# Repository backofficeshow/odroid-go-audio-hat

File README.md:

# odroid-go-audio-hat
An I2S Audio Hat for stereo sound from the odroid-go

UPDATE: The live build stream! https://youtu.be/j9-wCR7noaQ

1) A Manual Mod Was Made:

https://youtu.be/pp_DPHiUhcc

2) A SPI option conceived and failed:

https://youtu.be/Ehr8WgxajMo

https://www.youtube.com/watch?v=8DnR3sBm568

3) This forum thread provided the answers:

https://forum.odroid.com/viewtopic.php?f=158&t=31853&p=231227#p231227

crashoverride knows all the magic gpio runes!

4) The results are this archive!

https://www.youtube.com/watch?v=rQte53dfJiA

https://www.youtube.com/backofficeshow

Come chat with me on discord https://discord.gg/6UB4Zj7

Useful Links

PCM5102 Datasheet:

http://www.ti.com/lit/ds/slas764b/slas764b.pdf

Odroid-go Overview:

https://www.hardkernel.com/main/products/prdt_info.php?g_code=G152875062626

Odroid-go IO Information:

https://wiki.odroid.com/odroid_go/odroid_go#odroid-go_header_p2_description

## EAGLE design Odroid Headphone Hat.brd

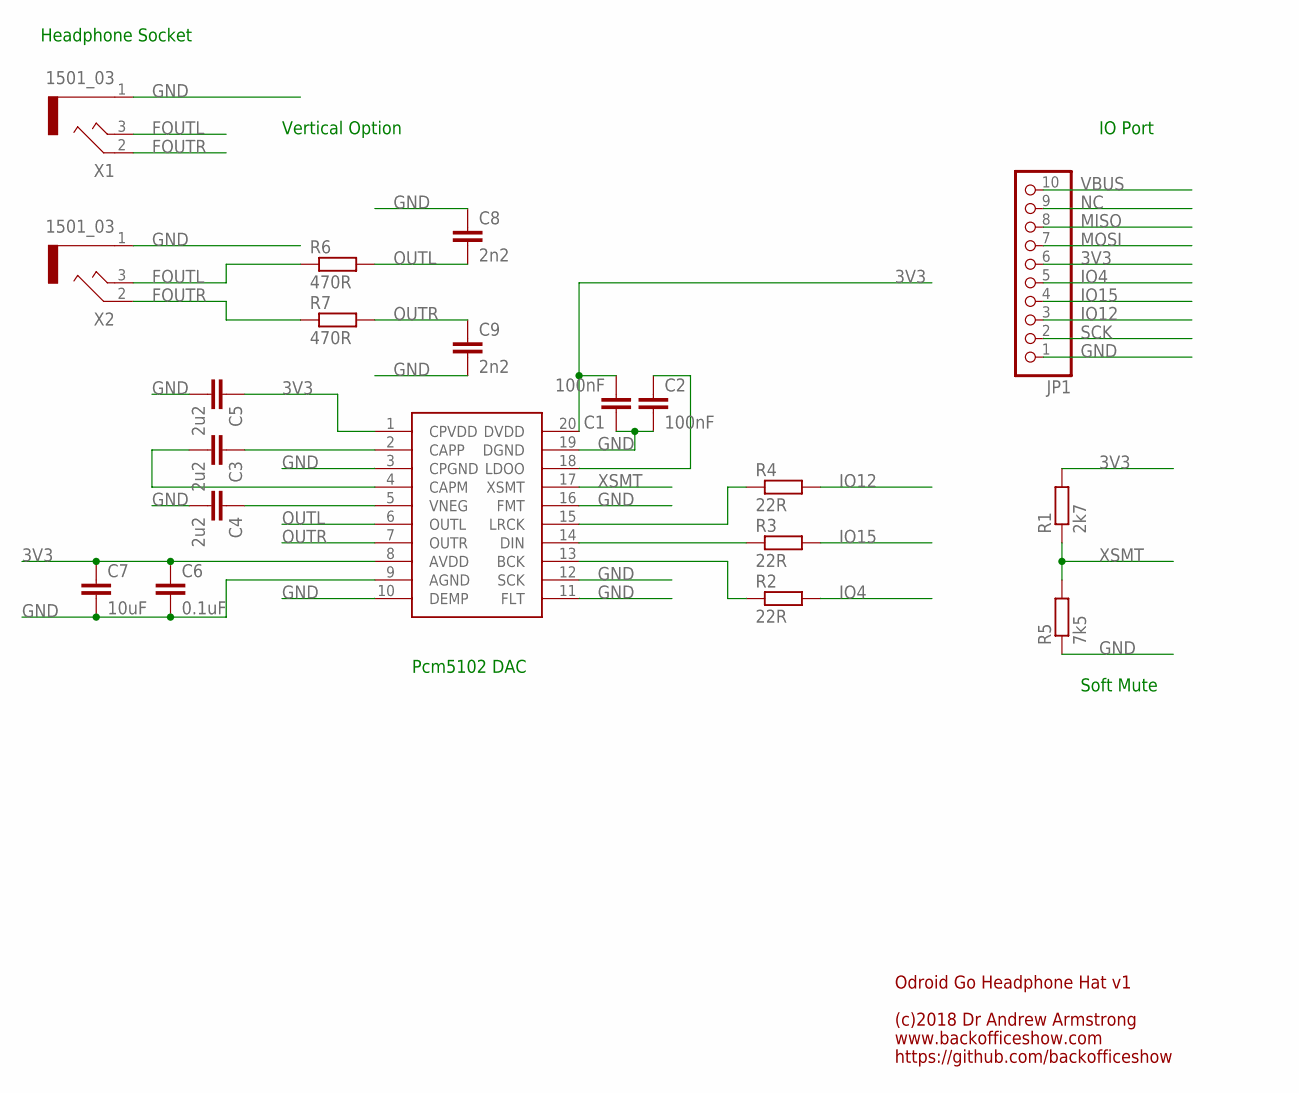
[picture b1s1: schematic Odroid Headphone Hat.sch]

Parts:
C1, C2: 100nF; C0603
C3, C4, C5: 2u2; C0603
C6: 0.1uF; C0603
C7: 10uF; C0603
C8, C9: 2n2; C0603
JP1: PINHD-1X10/90; 1X10/90
R1: 2k7; R0603
R2, R3, R4: 22R; R0603
R5: 7k5; R0603
R6, R7: 470R; R0603
U$1: PCM5102; TSSOP20
X1, X2: 1501_03

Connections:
3V3: C1.2, C5.1, C6.1, C7.1, JP1.6, R1.2, U$1.1 (CPVDD), U$1.8 (AVDD), U$1.20 (DVDD)
FOUTL: R6.1, X1.3, X2.3
FOUTR: R7.1, X1.2, X2.2
GND: C1.1, C2.2, C4.2, C5.2, C6.2, C7.2, C8.1, C9.2, JP1.1, R5.1, U$1.3 (CPGND), U$1.9 (AGND), U$1.10 (DEMP), U$1.11 (FLT), U$1.12 (SCK), U$1.16 (FMT), U$1.19 (DGND), X1.1, X2.1
IO4: JP1.5, R2.2
IO12: JP1.3, R4.2
IO15: JP1.4, R3.2
MISO: JP1.8
MOSI: JP1.7
unnamed: R2.1, U$1.13 (BCK)
unnamed: R3.1, U$1.14 (DIN)
unnamed: R4.1, U$1.15 (LRCK)
unnamed: C2.1, U$1.18 (LDOO)
unnamed: C3.1, U$1.2 (CAPP)
unnamed: C3.2, U$1.4 (CAPM)
unnamed: C4.1, U$1.5 (VNEG)
NC: JP1.9
OUTL: C8.2, R6.2, U$1.6 (OUTL)
OUTR: C9.1, R7.2, U$1.7 (OUTR)
SCK: JP1.2
VBUS: JP1.10
XSMT: R1.1, R5.2, U$1.17 (XSMT)

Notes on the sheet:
Odroid Go Headphone Hat v1
(c)2018 Dr Andrew Armstrong
www.backofficeshow.com
https://github.com/backofficeshow
Soft Mute
IO Port
Pcm5102 DAC
Headphone Socket
Vertical Option

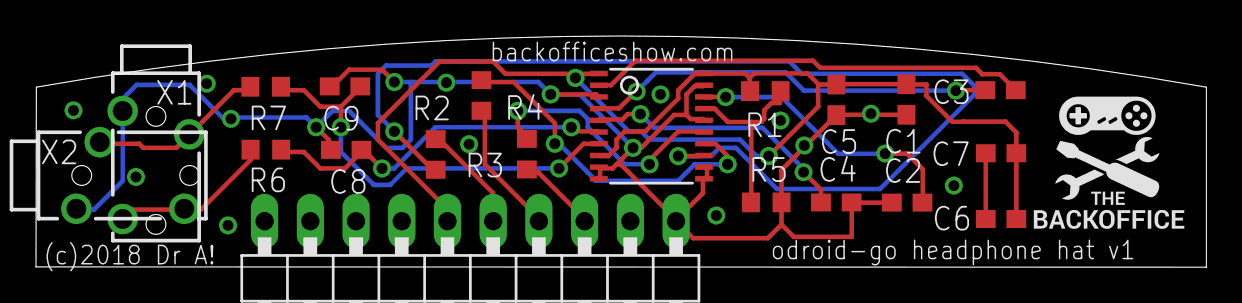
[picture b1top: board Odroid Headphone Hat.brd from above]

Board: 2 copper layers, 65.0 x 12.8 mm, 20 parts (0 on the bottom side), 17 nets.

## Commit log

2018-08-09 v1 Upload of the hat schematic and board
    Uploaded in eagle format, ready to be fabricated and tested
2018-08-10 A few tweeks
2018-08-10 Vias Tented ready for print
2018-08-10 Just a dimensional tweek
2018-08-16 tweeks to get working - no headphone mod yet
